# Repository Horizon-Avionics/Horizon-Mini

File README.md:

# H²

## Building an open source flight logger

### By Scooter Y and Liam G

------

#### About:

The Goal of this project was to build a simpler datalogger for model rockets to collect the info needed for most rocketiers from multiple sensors including an IMU and Baro. We built this as a dev board so when we eventually produce the larger V1 board, we can weed out issues before spending $400.

#### Features:

- This whole board is under $50 USD.
- One ARMCortex M0+ MCU
- IMU and Barometer
- SD and NAND Datalogging

##### Checkout locally

1. `git clone https://github.com/Horizon-Avionics/Horizon-Mini`

2. Open the corresponding folder in KiCad 9.0

### Some Photos So Far

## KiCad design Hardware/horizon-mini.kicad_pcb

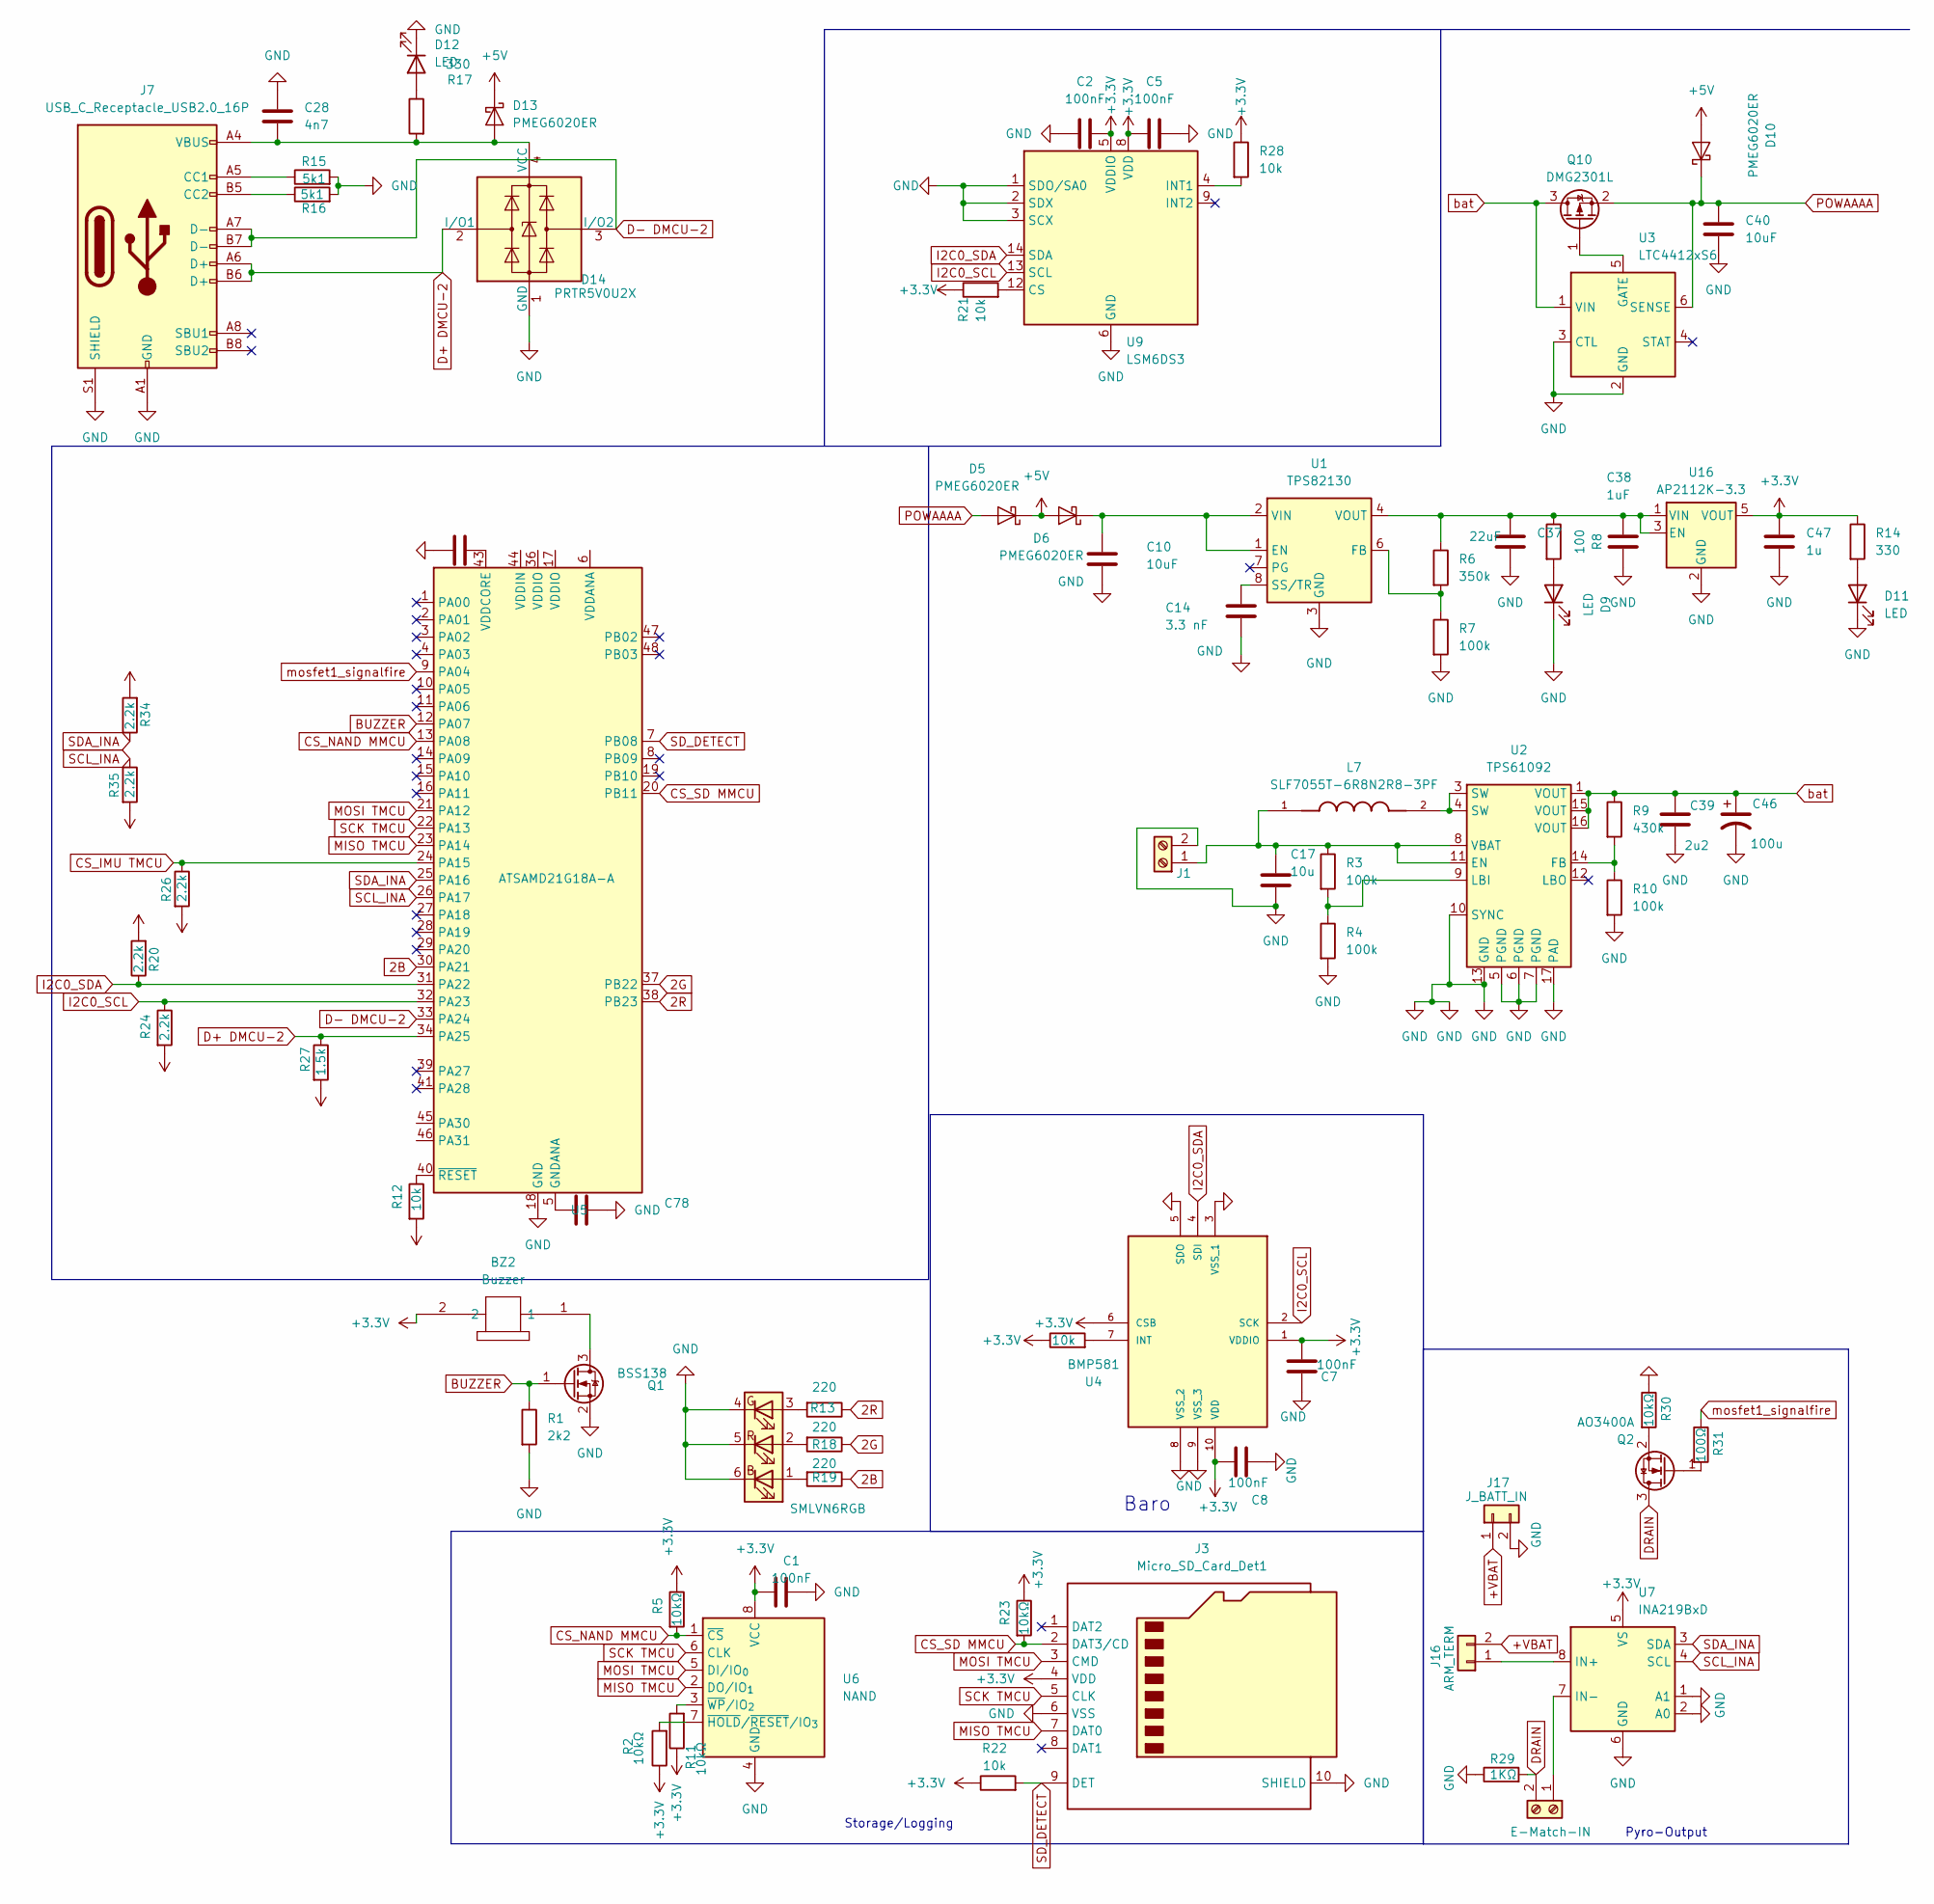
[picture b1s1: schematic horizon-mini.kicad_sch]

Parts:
BZ2: Buzzer; MLT-8530_JHE
C1, C2, C5, C7, C8, C78: 100nF; C_0402_1005Metric
C6: F1uF; C_0402_1005Metric
C10, C40: 10uF; C_0402_1005Metric
C14: 3.3 nF; C_0402_1005Metric
C17: 10u; C_0402_1005Metric
C28: 4n7; C_0402_1005Metric
C37: 22uF; C_0402_1005Metric
C38: 1uF; C_0402_1005Metric
C39: 2u2; C_0402_1005Metric
C46: 100u; C_0402_1005Metric
C47: 1u; C_0402_1005Metric
D1: SMLVN6RGB; LED_ROHM_SMLVN6
D5, D6, D10, D13: PMEG6020ER; Nexperia_CFP3_SOD-123W
D9, D11, D12: LED; LED_0603_1608Metric
D14: PRTR5V0U2X; SOT-143
J1: Screw_Terminal_01x02; TerminalBlock_Phoenix_MPT-0,5-2-2.54_1x02_P2.54mm_Horizontal
J3: Micro_SD_Card_Det1; microSD_HC_Hirose_DM3D-SF
J4: E-Match-IN; TerminalBlock_Phoenix_MPT-0,5-2-2.54_1x02_P2.54mm_Horizontal
J7: USB_C_Receptacle_USB2.0_16P; USB_C_Receptacle_GCT_USB4105-xx-A_16P_TopMnt_Horizontal
J16: ARM_TERM; PinHeader_1x02_P1.27mm_Vertical
J17: J_BATT_IN; PinHeader_1x02_P1.27mm_Vertical
L7: SLF7055T-6R8N2R8-3PF; L_7.3x7.3_H4.5; PARTREV N/A
Q1: BSS138; SOT-23
Q2: AO3400A; SOT-23
Q10: DMG2301L; SOT-23
R1: 2k2; R_0402_1005Metric
R2, R5, R11, R23, R30: 10kΩ; R_0402_1005Metric
R3, R4, R7, R10: 100k; R_0402_1005Metric
R6: 350k; R_0402_1005Metric
R8: 100; R_0402_1005Metric
R9: 430k; R_0402_1005Metric
R12, R21, R22, R28, R33: 10k; R_0402_1005Metric
R13, R18, R19: 220; R_0402_1005Metric
R14, R17: 330; R_0402_1005Metric
R15, R16: 5k1; R_0402_1005Metric
R20, R24, R26, R34, R35: 2.2k; R_0402_1005Metric
R27: 1.5k; R_0402_1005Metric
R29: 1KΩ; R_0402_1005Metric
R31: 100Ω; R_0402_1005Metric
U1: TPS82130; Texas_SIL0008D_MicroSiP-8-1EP_2.8x3mm_P0.65mm_EP1.1x1.9mm_T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
U2: TPS61092; Texas_RSA_VQFN-16-1EP_4x4mm_P0.65mm_EP2.7x2.7mm_ThermalVias
U3: LTC4412xS6; TSOT-23-6
U4: BMP581; Manufacturer_Part_Number BMP581
U5: ATSAMD21G18A-A; TQFP-48_7x7mm_P0.5mm
U6: NAND; SOIC-8_5.3x5.3mm_P1.27mm
U7: INA219BxD; SOIC-8_3.9x4.9mm_P1.27mm
U9: LSM6DS3; LGA-14_3x2.5mm_P0.5mm_LayoutBorder3x4y
U16: AP2112K-3.3; SOT-23-5

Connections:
2B: R19.1, U5.30 (PA21)
2G: R18.1, U5.37 (PB22)
2R: R13.1, U5.38 (PB23)
+3.3V: BZ2.2, C1.1, C2.2, C5.2, C7.2, C8.2, C47.1, J3.4 (VDD), R2.1, R5.1, R11.1, R12.2, R14.1, R20.2, R21.1, R22.1, R23.1, R24.2, R26.2, R27.2, R28.1, R33.1, R34.2, R35.2, U4.1 (VDDIO), U4.6 (CSB), U4.10 (VDD), U6.8 (VCC), U7.5 (VS), U9.5 (VDDIO), U9.8 (VDD), U16.5 (VOUT)
+5V: D5.1 (K), D6.2 (A), D10.2 (A), D13.1 (K)
+VBAT: J16.2, J17.1
BUZZER: Q1.1 (G), R1.1, U5.12 (PA07)
CS_IMU TMCU: R26.1, U5.24 (PA15)
CS_NAND MMCU: R5.2, U5.13 (PA08), U6.1 (~CS)
CS_SD MMCU: J3.2 (DAT3/CD), R23.2, U5.20 (PB11)
D+ DMCU-2: D14.2 (I/O1), J7.A6 (D+), J7.B6 (D+), R27.1, U5.34 (PA25)
D- DMCU-2: D14.3 (I/O2), J7.A7 (D-), J7.B7 (D-), U5.33 (PA24)
DRAIN: J4.2, Q2.3 (D), R29.2
GND: C1.2, C2.1, C5.1, C6.2, C7.1, C8.1, C10.2, C14.2, C17.2, C28.1, C37.2, C38.2, C39.2, C40.2, C46.2, C47.2, C78.1, D1.4 (GK), D1.5 (RK), D1.6 (BK), D9.1 (K), D11.1 (K), D12.1 (K), D14.1 (GND), J1.2, J3.6 (VSS), J3.10 (SHIELD), J7.A1 (GND), J7.A12 (GND), J7.B1 (GND), J7.B12 (GND), J7.S1 (SHIELD), J17.2, Q1.2 (S), R1.2, R4.2, R7.2, R10.2, R15.2, R16.2, R29.1, R30.1, U1.3 (GND), U1.9 (GND), U2.5 (PGND), U2.6 (PGND), U2.7 (PGND), U2.10 (SYNC), U2.13 (GND), U2.17 (PAD), U3.2 (GND), U3.3 (CTL), U4.3 (VSS_1), U4.5 (SDO), U4.8 (VSS_2), U4.9 (VSS_3), U5.18 (GND), U5.35 (GND), U5.42 (GND), U6.4 (GND), U7.1 (A1), U7.2 (A0), U7.6 (GND), U9.1 (SDO/SA0), U9.2 (SDX), U9.3 (SCX), U9.6 (GND), U9.7 (GND), U16.2 (GND); also elsewhere on the board
I2C0_SCL: R24.1, U4.2 (SCK), U5.32 (PA23), U9.13 (SCL)
I2C0_SDA: R20.1, U4.4 (SDI), U5.31 (PA22), U9.14 (SDA)
MISO TMCU: J3.7 (DAT0), U5.23 (PA14), U6.2 (DO/IO_{1})
MOSI TMCU: J3.3 (CMD), U5.21 (PA12), U6.5 (DI/IO_{0})
unnamed: D1.1 (BA), R19.2
unnamed: D1.3 (GA), R13.2
unnamed: D1.2 (RA), R18.2
unnamed: C10.1, D6.1 (K), U1.1 (EN), U1.2 (VIN)
unnamed: D9.2 (A), R8.2
unnamed: D11.2 (A), R14.2
unnamed: D12.2 (A), R17.1
unnamed 25: C28.2, D13.2 (A), D14.4 (VCC), J7.A4 (VBUS), J7.A9 (VBUS), J7.B4 (VBUS), J7.B9 (VBUS), R17.2; also elsewhere on the board
unnamed: C17.1, J1.1, L7.1, R3.1, U2.8 (VBAT), U2.11 (EN)
unnamed: J4.1, U7.7 (IN-)
unnamed: J7.A5 (CC1), R15.1
unnamed: J7.B5 (CC2), R16.1
unnamed: J16.1, U7.8 (IN+)
unnamed: L7.2, U2.3 (SW), U2.4 (SW)
unnamed: BZ2.1, Q1.3 (D)
unnamed: Q2.1 (G), R31.2
unnamed: Q2.2 (S), R30.2
unnamed: Q10.1 (G), U3.5 (GATE)
unnamed: R6.2, R7.1, U1.6 (FB)
unnamed: C14.1, U1.8 (SS/TR)
unnamed: R9.2, R10.1, U2.14 (FB)
unnamed: R3.2, R4.1, U2.9 (LBI)
unnamed: R33.2, U4.7 (INT)
unnamed: C78.2, U5.5 (GNDANA)
unnamed: C6.1, U5.43 (VDDCORE)
unnamed: R12.1, U5.40 (~RESET)
unnamed: R2.2, U6.7 (~HOLD/~RESET/IO_{3})
unnamed: R11.2, U6.3 (~WP/IO_{2})
unnamed: R21.2, U9.12 (CS)
unnamed: R28.2, U9.4 (INT1)
unnamed: C37.1, C38.1, R6.1, R8.1, U1.4 (VOUT), U1.5 (VOUT), U16.1 (VIN), U16.3 (EN)
POWAAAA: C40.1, D5.2 (A), D10.1 (K), Q10.2 (S), U3.6 (SENSE)
SCK TMCU: J3.5 (CLK), U5.22 (PA13), U6.6 (CLK)
SCL_INA: R35.1, U5.26 (PA17)
SDA_INA: R34.1, U5.25 (PA16)
SD_DETECT: J3.9 (DET), R22.2, U5.7 (PB08)
bat: C39.1, C46.1, Q10.3 (D), R9.1, U2.1 (VOUT), U2.15 (VOUT), U2.16 (VOUT), U3.1 (VIN)
mosfet1_signalfire: R31.1, U5.9 (PA04)

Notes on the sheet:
Pyro-Output
Storage/Logging
Baro

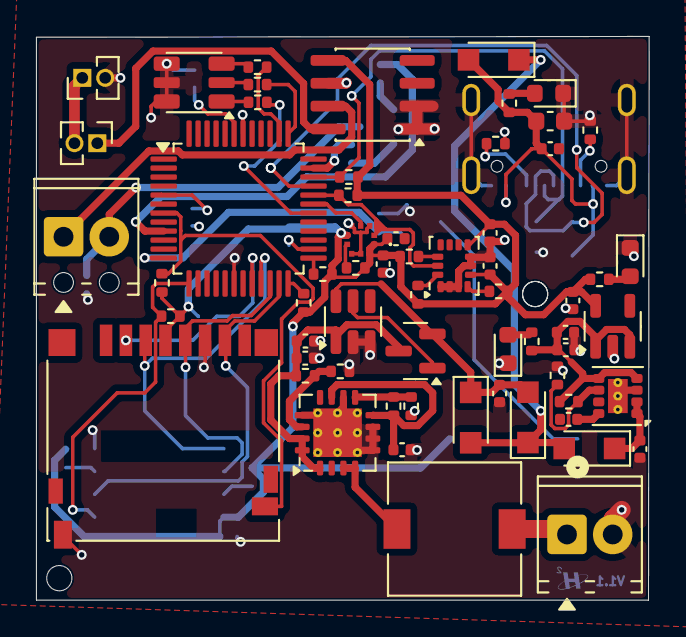
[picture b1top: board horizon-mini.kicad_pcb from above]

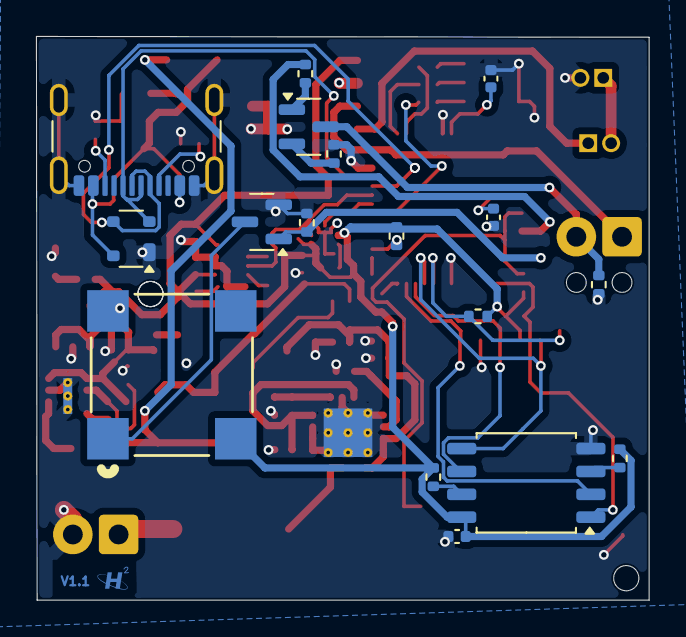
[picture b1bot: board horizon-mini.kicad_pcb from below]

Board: 2 copper layers, 34.0 x 31.3 mm, 79 parts (17 on the bottom side), 55 nets.

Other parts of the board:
C29: 100n; C_0603_1608Metric

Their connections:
GND: C29.1; also elsewhere on the board
unnamed 25: C29.2; also elsewhere on the board

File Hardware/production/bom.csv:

Designator,Footprint,Quantity,Value,LCSC Part #
"_4, _3, _2, ",,4,,
BZ2,MLT-8530_JHE,1,Buzzer,
"C1, C2, C3, C4, C5",0603,5,100nF,
"C10, C40",0603,2,10uF,
"C11, C7, C8, C9",0402,4,0.1uF,
C12,0402,1,10uF,
C14,0603,1,3.3 nF,
C17,0603,1,10u,
C28,0603,1,4n7,
C29,0603,1,100n,
C37,0603,1,22uF,
C38,0603,1,1uF,
C39,0603,1,2u2,
C46,1206,1,100u,
C47,0603,1,1u,
C6,0603,1,F1uF,
C78,0402,1,100nF,
D1,LED_ROHM_SMLVN6,1,SMLVN6RGB,
"D10, D13, D5, D6",Nexperia_CFP3_SOD-123W,4,PMEG6020ER,
"D11, D12, D2, D9",0603,4,LED,
D14,SOT-143,1,PRTR5V0U2X,
F2,0603,1,Polyfuse,
J1,"TerminalBlock_Phoenix_MPT-0,5-2-2.54_1x02_P2.54mm_Horizontal",1,Screw_Terminal_01x02,
J16,PinHeader_1x02_P2.00mm_Vertical_SMD_Pin1Left,1,arming terminal,
J2,TerminalBlock_MetzConnect_Type059_RT06302HBWC_1x02_P3.50mm_Horizontal,1,Conn_01x02_Pin,
J3,microSD_HC_Hirose_DM3D-SF,1,Micro_SD_Card_Det1,
J7,USB_C_Receptacle_GCT_USB4105-xx-A_16P_TopMnt_Horizontal,1,USB_C_Receptacle_USB2.0_16P,
J8,PinHeader_2x03_P2.54mm_Vertical,1,Conn_02x03_Counter_Clockwise,
L7,L_7.3x7.3_H4.5,1,SLF7055T-6R8N2R8-3PF,
Q1,SOT-23,1,BSS138,
Q10,SOT-23,1,DMG2301L,
Q2,SOT-23,1,IRLML6402,
R1,0603,1,2k2,
"R10, R3, R4, R7",0603,4,100k,
"R11, R2, R23",0603,3,10kΩ,
"R12, R21, R22, R25, R28, R29, R80",0603,7,10k,
"R13, R18, R19",0603,3,220,
"R14, R17",0603,2,330,
"R15, R16",0603,2,5k1,
"R20, R24, R26",0603,3,2.2k,
R27,0603,1,1.5k,
"R30, R8",0603,2,100,
R31,0603,1,1k,
R5,0402,1,10kΩ,
R6,0805,1,350k,
R9,0603,1,430k,
U1,Texas_SIL0008D_MicroSiP-8-1EP_2.8x3mm_P0.65mm_EP1.1x1.9mm_ThermalVias,1,TPS82130,
U16,SOT-23-5,1,AP2112K-3.3,
U2,Texas_RSA_VQFN-16-1EP_4x4mm_P0.65mm_EP2.7x2.7mm_ThermalVias,1,TPS61092,
U3,TSOT-23-6,1,LTC4412xS6,
U5,TQFP-48_7x7mm_P0.5mm,1,ATSAMD21G18A-A,
U6,SOIC-8_5.3x5.3mm_P1.27mm,1,NAND,
U7,ST_HLGA-10_2x2mm_P0.5mm_LayoutBorder3x2y,1,LPS22HB,
U9,LGA-14_3x2.5mm_P0.5mm_LayoutBorder3x4y,1,LSM6DS3,

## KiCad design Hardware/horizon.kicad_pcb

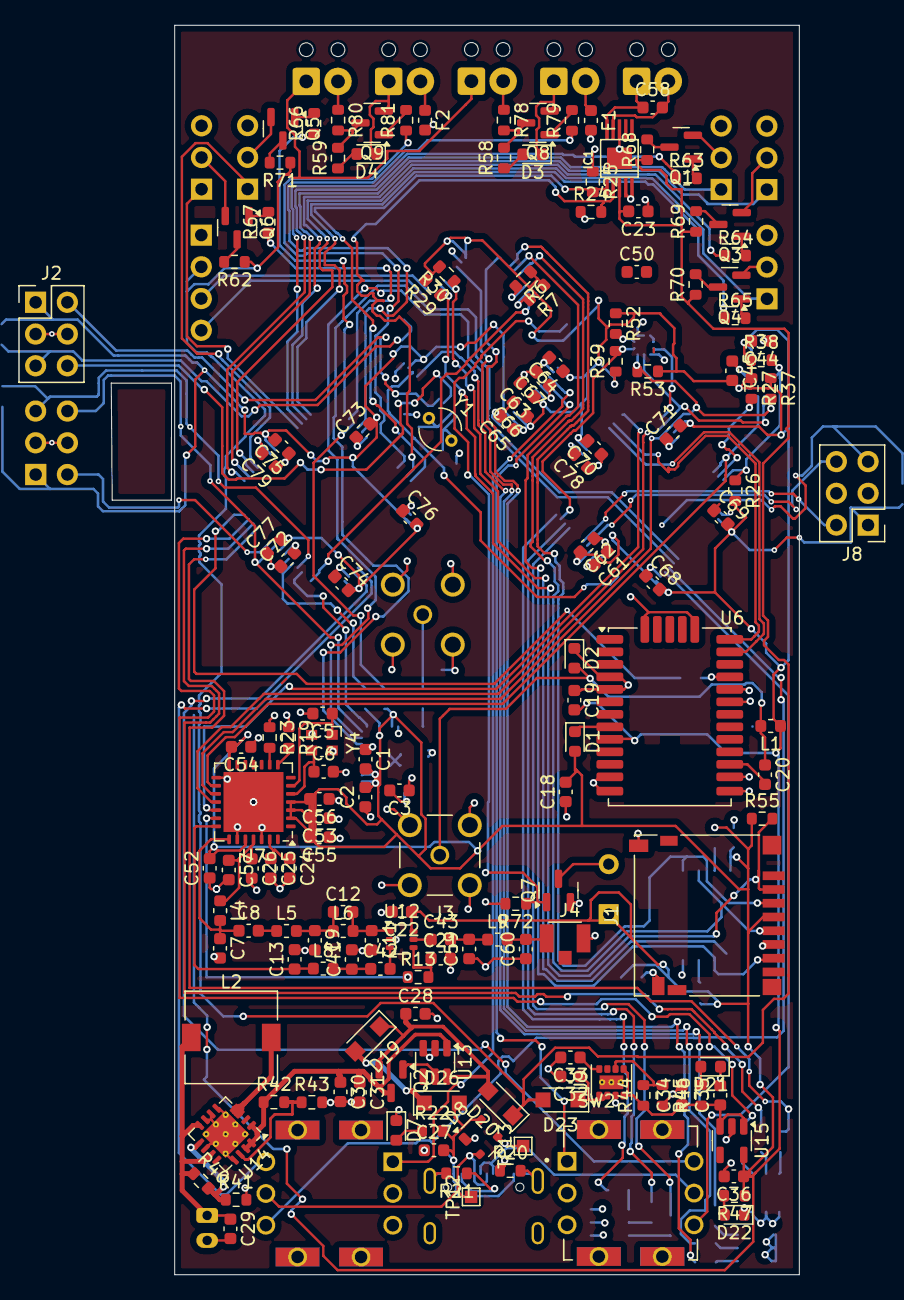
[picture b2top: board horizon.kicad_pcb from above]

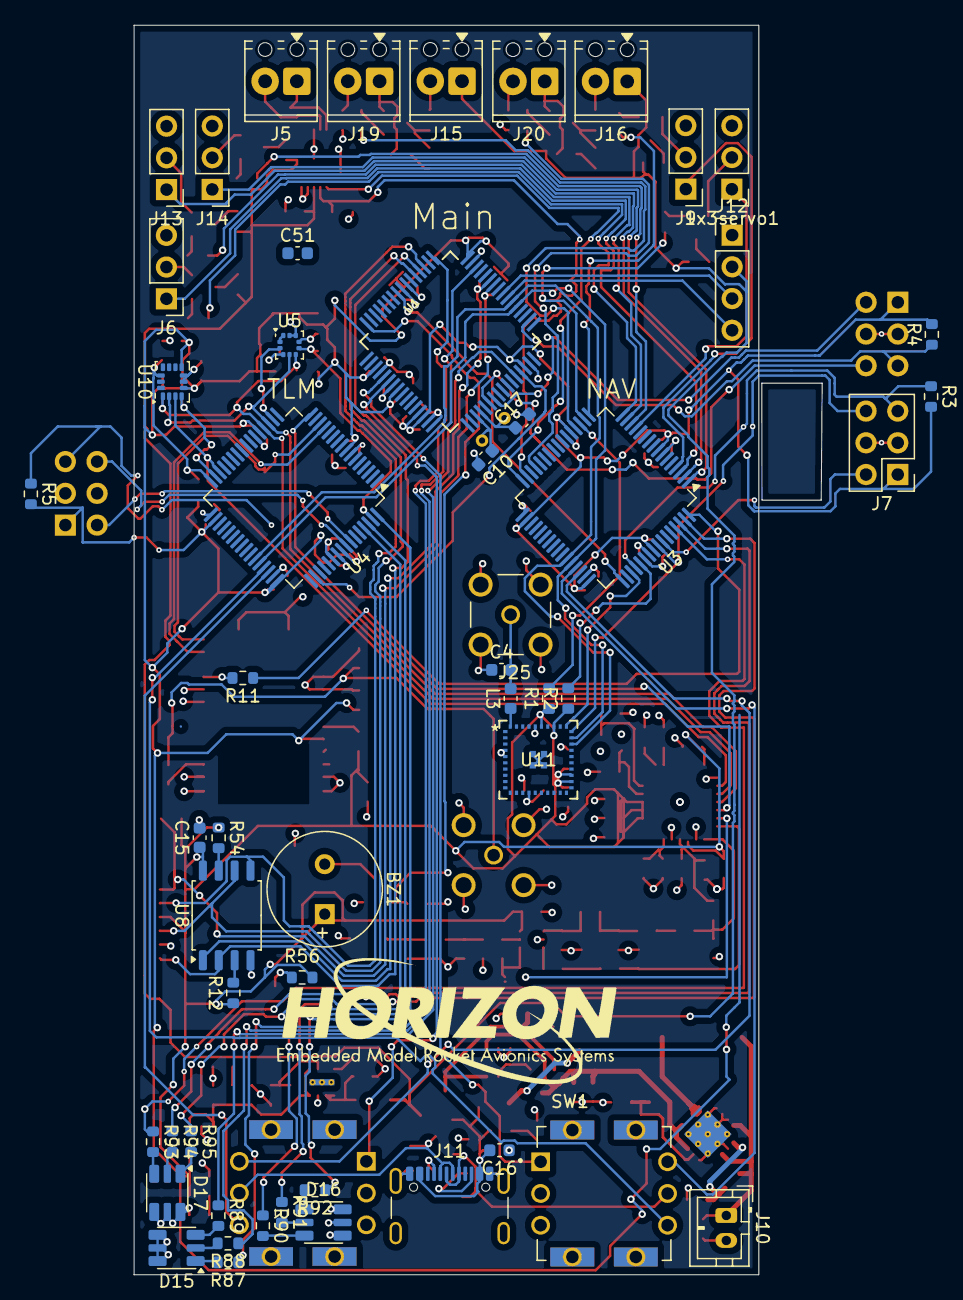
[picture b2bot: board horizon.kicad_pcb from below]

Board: 4 copper layers, 50.0 x 100.0 mm, 210 parts (53 on the bottom side), 164 nets.

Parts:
1x3servo1: Conn_01x03; PinHeader_1x03_P2.54mm_Vertical
BZ1: Buzzer; MagneticBuzzer_PUI_AT-0927-TT-6-R
C1, C2, C3, C23: 100 nF; C_0603_1608Metric
C4, C12: 1.2 pF; C_0603_1608Metric
C5, C6: 12 pF; C_0603_1608Metric
C7, C9, C13, C59: 2.2 pF; C_0603_1608Metric
C8: 1.5 pF; C_0603_1608Metric
C10, C17: 12pF; C_0603_1608Metric
C11, C41: 2.7 pF; C_0603_1608Metric
C15, C19, C20, C25, C44, C45, C50, C51, C52, C53, C54, C55, C56, C57, C58, C61, C62, C68, C69, C70, C71, C73, C74, C75, C76, C77, C78, C79: 100nF; C_0603_1608Metric
C16: 4n7; C_0603_1608Metric
C18, C67: 4.7uF; C_0603_1608Metric
C21, C22: 1nF; C_0603_1608Metric
C24, C26: 10nF; C_0603_1608Metric
C27: 100n; C_0603_1608Metric
C28, C32: 10uF; C_0603_1608Metric
C29: 10u; C_0603_1608Metric
C30: 2u2; C_0603_1608Metric
C31: 100u; C_0603_1608Metric
C33: 3.3 nF; C_0603_1608Metric
C34: 22uF; C_0603_1608Metric
C35, C63, C72: 1uF; C_0603_1608Metric
C36: 1u; C_0603_1608Metric
C42, C60: 1.8 pF; C_0603_1608Metric
C43: 1.0 pF; C_0603_1608Metric
C64, C65, C66: 0.1uF; C_0603_1608Metric
D1: D_Schottky; D_0603_1608Metric
D2: PESD5V‑S5ULC; D_0603_1608Metric
D3, D4, D7, D21, D22: LED; LED_0603_1608Metric
D8: PRTR5V0U2X; SOT-143
D15, D16, D17: SMLVN6RGB; LED_ROHM_SMLVN6
D19, D20, D23, D26: PMEG6020ER; Nexperia_CFP3_SOD-123W
F1, F2: Polyfuse; Fuse_0603_1608Metric
G**: LOGO
IC1: A3909; MSOP10-PAD
J1: Micro_SD_Card_Det1; microSD_HC_Hirose_DM3D-SF
J2, J7, J8: Conn_02x03_Counter_Clockwise; PinHeader_2x03_P2.54mm_Vertical
J3, J25: Conn_Coaxial; LPRS_SMA_CONNECTOR
J4: H9161TR-ND; HRS_U.FL-R-SMT_01_
J5: Screw_Term; TerminalBlock_Phoenix_MPT-0,5-2-2.54_1x02_P2.54mm_Horizontal
J6, J9, J13, J14: 1x3 servo; PinHeader_1x03_P2.54mm_Vertical
J10: Conn_01x02_Pin; JST_PH_B2B-PH-K_1x02_P2.00mm_Vertical
J11: USB_C_Receptacle_USB2.0_16P; USB_C_Receptacle_GCT_USB4105-xx-A_16P_TopMnt_Horizontal
J12: Conn_01x04; PinHeader_1x04_P2.54mm_Vertical
J15, J16: arming terminal; TerminalBlock_Phoenix_MPT-0,5-2-2.54_1x02_P2.54mm_Horizontal
J19, J20: Screw_Terminal_01x02; TerminalBlock_Phoenix_MPT-0,5-2-2.54_1x02_P2.54mm_Horizontal
L1: 47 nH; L_0603_1608Metric
L2: SLF7055T-6R8N2R8-3PF; L_7.3x7.3_H4.5
L3: 3.9 nH; L_0603_1608Metric
L4: 8.2 nH; L_0603_1608Metric
L5, L8: 6.8 nH; L_0603_1608Metric
L6, L9: 10 nH; L_0603_1608Metric
Q1, Q3, Q4, Q5, Q6, Q8, Q9: IRLML6402; SOT-23
Q2: DMG2301L; SOT-23
Q7: BSS138; SOT-23
R1, R2: 10 kΩ; R_0603_1608Metric
R3, R4, R5, R19, R23, R24, R25, R27, R37, R38, R39, R52, R53, R56, R78, R80: 10k; R_0603_1608Metric
R6, R7: 4.7k; R_0603_1608Metric
R11, R12, R54, R55: 10kΩ; R_0603_1608Metric
R13, R58, R59: 1k; R_0603_1608Metric
R20, R21: 5k1; R_0603_1608Metric
R22, R47: 330; R_0603_1608Metric
R26, R29, R30: R; R_0603_1608Metric
R40, R41, R43, R45, R62, R68, R69, R70, R71: 100k; R_0603_1608Metric
R42: 430k; R_0603_1608Metric
R44: 350k; R_0603_1608Metric
R46, R63, R64, R65, R66, R67, R79, R81: 100; R_0603_1608Metric
R72: 2k2; R_0603_1608Metric
R87, R88, R89, R90, R91, R92, R93, R94, R95: 220; R_0603_1608Metric
SW1, SW2: SW_SP3T; SW_NR01103ANG13-1C
TP12, TP13: TestPoint; TestPoint_Pad_1.0x1.0mm
U1: MMCU; QFP50P1200X1200X160-64N
U3: NMCU; TQFP-64_10x10mm_P0.5mm
U4: TMCU; TQFP-64_10x10mm_P0.5mm
U5: LPS22HB; ST_HLGA-10_2x2mm_P0.5mm_LayoutBorder3x2y
U6: GPS; Quectel_L96
U7: SX1276; QFN-28-1EP_6x6mm_P0.65mm_EP4.8x4.8mm
U8: NAND; SOIC-8_5.3x5.3mm_P1.27mm
U9: TPS82130; Texas_SIL0008D_MicroSiP-8-1EP_2.8x3mm_P0.65mm_EP1.1x1.9mm_T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
U10: LSM6DS3; LGA-14_3x2.5mm_P0.5mm_LayoutBorder3x4y
U11: BGM220SC12WGA2R
U12: PE4259; SOT-363_SC-70-6
U13: LTC4412xS6; TSOT-23-6
U14: TPS61092; Texas_RSA_VQFN-16-1EP_4x4mm_P0.65mm_EP2.7x2.7mm_ThermalVias
U15: AP2112K-3.3; SOT-23-5
Y1: Crystal; Crystal_AT310_D3.0mm_L10.0mm_Vertical
Y4: 32MHz; Crystal_SMD_Abracon_ABM10-4Pin_2.5x2.0mm

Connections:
1B: R87.1, U1.49 (D10/TX2/PWM)
1G: R88.1, U1.46 (D9/RX2/PWM)
1R: R89.1, U1.28 (D3/CAN-TX/PWM)
2B: R92.1, U4.64 (PB03)
2G: R91.1, U4.62 (PB01)
2R: R90.1, U4.61 (PB00)
3B: R95.1, U3.63 (PB02)
3G: R94.1, U3.62 (PB01)
3R: R93.1, U3.61 (PB00)
+3.3V: BZ1.1 (+), C1.2, C2.2, C15.1, C18.2, C19.2, C22.1, C36.1, C44.2, C45.2, C50.2, C51.2, C52.2, C53.2, C54.2, C55.2, C56.2, C62.2, C63.1, C64.1, C65.1, C66.1, C68.2, C69.2, C70.2, C71.2, C73.2, C74.2, C75.2, C76.2, C77.2, D1.2 (A), J1.4 (VDD), J2.1, J7.1, J8.1, L1.1, R1.1, R2.1, R3.2, R4.2, R5.2, R6.1, R7.1, R12.1, R26.2, R27.1, R29.2, R30.2, R37.1, R38.1, R39.1, R47.1, R52.1, R53.1, R54.1, R55.1, R56.1, U1.3 (VCC), U1.8 (VREGIN), U1.13 (VCCA), U1.14 (VREF-H), U1.21 (VBAT), U1.30 (VCC), U1.48 (VCC), U3.8 (VDDANA), U3.21 (VDDIO), U3.34 (VDDIO), U3.48 (VDDIO), U3.56 (VDDIN), U4.8 (VDDANA), U4.21 (VDDIO), U4.34 (VDDIO), U4.48 (VDDIO), U4.56 (VDDIN), U5.1 (Vdd_IO), U5.10 (VDD), U6.9 (VCC), U7.2 (VR_ANA), U7.3 (VBAT_ANA), U7.4 (VR_DIG), U7.14 (VBAT_DIG), U7.24 (VBAT_RF), U8.8 (VCC), U10.5 (VDDIO), U10.8 (VDD), U11.22 (VREGVDD), U11.23 (IOVDD), U11.33 (PC05), U11.35 (RESETn), U12.6 (VDD), U15.5 (VOUT)
+5V: C23.2, D20.1 (K), D23.2 (A), IC1.3 (VBB), J12.2, J15.1, J16.1, R62.1, R68.1, R69.1, R70.1, R71.1
BGM_CS: U3.51 (PA27), U11.31 (PC03)
BGM_INT: R2.2, U3.53 (PA28)
BGM_RESET: R1.2, U3.19 (PA10)
BUZZER: Q7.1 (G), R72.1, U1.64 (D5/PWM)
CAM_RX: J12.3, U1.40 (D1/TX1/TOUCH)
CAM_TX: J12.4, U1.39 (D0/RX1/TOUCH)
CS_BARO TMCU: R39.2, U4.63 (PB02), U5.6 (~CS)
CS_IMU TMCU: R26.1, R38.2, U4.32 (PA15), U10.12 (CS)
CS_NAND MMCU: R30.1, U1.43 (D15/A1/TOUCH), U8.1 (~CS)
CS_SD MMCU: J1.2 (DAT3/CD), R29.1, R55.2, U1.42 (D25/PWM/TOUCH)
D+ DMCU-1: SW1.2, U3.45 (PA24)
D+ DMCU-2: SW1.4, U4.45 (PA24)
D+ MMCU: SW1.1, U1.5 (USB-P)
D- DMCU-1: SW2.2, U3.46 (PA25)
D- DMCU-2: SW2.4, U4.46 (PA25)
D- MMCU: SW2.1, U1.6 (USB-M)
DIR1: IC1.2 (IN2), R24.2, U3.31 (PA14)
GND: 1x3servo1.3, C1.1, C2.1, C3.1, C4.1, C5.2, C6.2, C7.2, C9.2, C10.2, C11.2, C13.2, C15.2, C16.1, C17.2, C18.1, C19.1, C21.2, C22.2, C23.1, C24.2, C25.2, C26.2, C27.1, C28.2, C29.2, C30.2, C31.2, C32.2, C33.2, C34.2, C35.2, C36.2, C41.2, C44.1, C45.1, C50.1, C51.1, C52.1, C53.1, C54.1, C55.1, C56.1, C57.2, C59.1, C60.1, C61.1, C62.1, C63.2, C64.2, C65.2, C66.2, C67.2, C68.1, C69.1, C70.1, C71.1, C72.1, C73.1, C74.1, C75.1, C76.1, C77.1, C78.1, C79.1, D2.1 (K), D7.1 (K), D8.1 (GND), D15.4 (GK), D15.5 (RK), D15.6 (BK), D16.4 (GK), D16.5 (RK), D16.6 (BK), D17.4 (GK), D17.5 (RK), D17.6 (BK), D21.1 (K), D22.1 (K), F1.2, F2.2, IC1.4 (IN3), IC1.5 (IN4), IC1.8 (GND), IC1.TP (GND), J1.6 (VSS), J1.10 (SHIELD), J2.3, J2.4, J3.G1, J3.G2, J3.G3, J3.G4, J4.2 (Ext), J6.3, J7.3, J7.4, J8.3, J8.4, J9.3, J10.2, J11.A1 (GND), J11.A12 (GND), J11.B1 (GND), J11.B12 (GND), J11.S1 (SHIELD), J12.1, J13.3, J14.3, J25.G1, J25.G2, J25.G3, J25.G4, Q7.2 (S), R19.1, R20.2, R21.2, R23.1, R24.1, R25.1, R41.2, R43.2, R45.2, R72.2, U1.4 (VSS), U1.15 (VREF-L), U1.16 (VSSA), U1.31 (VSS), U1.47 (VSS), U3.22 (GND), U3.33 (GND), U3.47 (GND), U3.54 (GND), U4.22 (GND), U4.33 (GND), U4.47 (GND), U4.54 (GND), U5.3 (GND), U5.8 (GND), U5.9 (GND), U6.4 (GND), U6.5 (GND), U6.10 (GND), U6.11 (GND), U6.12 (GND), U6.13 (GND), U6.14 (GND), U6.15 (GND), U6.18 (GND), U6.19 (GND), U6.21 (GND), U6.22 (GND), U6.27 (GND), U6.31 (GND), U7.15 (GND), U7.23 (GND), U7.26 (GND), U7.29 (GND), U8.4 (GND), U9.3 (GND), U9.9 (GND), U10.6 (GND), U10.7 (GND), U11.4 (GND), U11.5 (GND), U11.36 (GND), U11.41 (GND), U11.42 (GND), U11.43 (GND), U11.44 (GND), U12.2 (GND), U13.2 (GND), U13.3 (CTL), U14.5 (PGND), U14.6 (PGND), U14.7 (PGND), U14.10 (SYNC), U14.13 (GND), U14.17 (PAD), U15.2 (GND), Y4.2, Y4.4
I2C0_SCL: U1.37 (D19/A5/SCL0/TOUCH), U3.44 (PA23), U4.44 (PA23), U11.29 (PC01)
I2C0_SDA: U1.38 (D18/A4/SDA0/TOUCH), U3.43 (PA22), U4.43 (PA22), U11.28 (PC00)
INTERRUPT TMCU: R27.2, U4.31 (PA14), U10.4 (INT1)
MISO TMCU: R37.2, R53.2, U4.20 (PA11), U5.5 (SA0), U7.17 (MISO), U10.1 (SDO/SA0)
MOSI TMCU: U4.19 (PA10), U5.4 (SDA), U7.18 (MOSI), U10.2 (SDX)
NAND_MISO MMCU: J1.7 (DAT0), U1.52 (D12/MISO), U8.2 (DO/IO_{1})
NAND_MOSI MMCU: J1.3 (CMD), U1.51 (D11/MOSI), U8.5 (DI/IO_{0})
unnamed: 1x3servo1.2, Q6.2 (S)
unnamed: BZ1.2 (-), Q7.3 (D)
unnamed: C8.2, L5.1
unnamed: C9.1, C12.1, L5.2, L6.1
unnamed: C41.1, C42.1, L8.2
unnamed: C43.2, C59.2, L9.1
unnamed: D1.1 (K), U6.8 (V_BCKP)
unnamed: C20.1, D2.2 (A), J3.1 (In), L1.2
unnamed: D3.2 (A), R58.1
unnamed: D3.1 (K), J19.1, Q8.2 (S)
unnamed: D4.2 (A), R59.1
unnamed: D4.1 (K), J20.1, Q9.2 (S)
unnamed: D7.2 (A), R22.1
unnamed: D8.2 (I/O1), J11.A6 (D+), J11.B6 (D+), SW1.3, TP12.1
unnamed: D8.3 (I/O2), J11.A7 (D-), J11.B7 (D-), SW2.3, TP13.1
unnamed: D15.1 (BA), R87.2
unnamed: D15.3 (GA), R89.2
unnamed: D15.2 (RA), R88.2
unnamed: D16.1 (BA), R92.2
unnamed: D16.3 (GA), R90.2
unnamed: D16.2 (RA), R91.2
unnamed: D17.1 (BA), R95.2
unnamed: D17.3 (GA), R93.2
unnamed: D17.2 (RA), R94.2
unnamed: D21.2 (A), R46.2
unnamed: D22.2 (A), R47.2
unnamed: C32.1, D23.1 (K), U9.1 (EN), U9.2 (VIN)
unnamed: C16.2, C27.2, D8.4 (VCC), D26.2 (A), J11.A4 (VBUS), J11.A9 (VBUS), J11.B4 (VBUS), J11.B9 (VBUS), R22.2
unnamed: C58.1, IC1.10 (OUT1), J5.1
unnamed: C58.2, IC1.9 (OUT2), J5.2
unnamed: C60.2, J4.1 (In), L9.2
unnamed: J6.2, Q4.2 (S)
unnamed: J9.2, Q5.2 (S)
unnamed: C29.1, J10.1, L2.1, R40.1, U14.8 (VBAT), U14.11 (EN)
unnamed: J11.A5 (CC1), R20.1
unnamed: J11.B5 (CC2), R21.1
unnamed: J13.2, Q3.2 (S)
unnamed: J14.2, Q1.2 (S)
unnamed: J15.2, R78.1
unnamed: J16.2, R80.1
unnamed: F1.1, J19.2
unnamed: F2.1, J20.2
unnamed: C4.2, J25.1 (In), L3.2
unnamed: L2.2, U14.3 (SW), U14.4 (SW)
unnamed: Q1.3 (D), R68.2
unnamed: Q1.1 (G), R63.2
unnamed: Q2.1 (G), U13.5 (GATE)
unnamed: Q3.3 (D), R69.2
unnamed: Q3.1 (G), R64.2
unnamed: Q4.3 (D), R70.2
unnamed: Q4.1 (G), R65.2
unnamed: Q5.3 (D), R71.2
unnamed: Q5.1 (G), R66.2
unnamed: Q6.3 (D), R62.2
unnamed: Q6.1 (G), R67.2
unnamed: Q8.3 (D), R58.2, R78.2
unnamed: Q8.1 (G), R79.2
unnamed: Q9.3 (D), R59.2, R80.2
unnamed: Q9.1 (G), R81.2
unnamed: C17.1, U1.20 (EXTAL32), Y1.1
unnamed: C67.1, U1.7 (VOUT3V3)
unnamed: C10.1, U1.19 (XTAL32), Y1.2
unnamed: C79.2, U3.7 (GNDANA)
unnamed: C72.2, U3.55 (VDDCORE)
unnamed: C78.2, U4.7 (GNDANA)
unnamed: C61.2, U4.55 (VDDCORE)
unnamed: R52.2, U5.7 (INT_DRDY)
unnamed: C20.2, U6.16 (RF_OUT)
unnamed: R11.2, U6.23 (~RESET)
unnamed: R19.2, U7.8 (DIO0)
unnamed: R23.2, U7.9 (DIO1)
unnamed: C24.1, C25.1, U7.27 (PA_BOOST)
unnamed: R54.2, U8.7 (~HOLD/~RESET/IO_{3})
unnamed: R12.2, U8.3 (~WP/IO_{2})
unnamed: R44.2, R45.1, U9.6 (FB)
unnamed: C33.1, U9.8 (SS/TR)
unnamed: L3.1, U11.40 (ANT_OUT)
unnamed: C3.2, U11.14 (DECOUPLE)
unnamed: C21.1, R13.2, U12.4 (CTRL)
unnamed: C11.1, C12.2, L6.2, U12.1 (RF1)
unnamed: C42.2, U12.3 (RF2)
unnamed: C43.1, U12.5 (RFIN)
unnamed: R42.2, R43.1, U14.14 (FB)
unnamed: R40.2, R41.1, U14.9 (LBI)
unnamed: C34.1, C35.1, R44.1, R46.1, U9.4 (VOUT), U9.5 (VOUT), U15.1 (VIN), U15.3 (EN)
POWAAAA: C28.1, D19.1 (K), D20.2 (A), Q2.2 (S), U13.6 (SENSE)
PTA12: U1.29 (D4/CAN-RX/PWM), U4.50 (PB23)
PTD4: U1.57 (D2), U3.49 (PB22)
PWM1: IC1.1 (IN1), R25.2, U3.32 (PA15)
RFI_HF: C13.1, L8.1, U7.21 (RFI_HF)
RFO_HF: C7.1, C8.1, L4.2, U7.22 (RFO_HF)
RF_CS: U4.16 (PA07), U7.19 (NSS)
RS_GPS TMCU: R11.1, U3.64 (PB03)
RX TMCU: U4.14 (PA05), U6.26 (RXD1)
RXTX: R13.1, U7.20 (RXTX/RF_MOD)
SCK TMCU: U4.18 (PA09), U5.2 (SCL)
SD_DETECT: J1.9 (DET), R56.2
SERVO1: J14.1, U3.1 (PA00)
SERVO2: J13.1, U3.2 (PA01)
SERVO3: J6.1, U3.3 (PA02)
SERVO4: J9.1, U3.4 (PA03)
SERVO5: 1x3servo1.1, U3.13 (PA04)
SPI0_SCK MMCU: J1.5 (CLK), U1.53 (D28/A17), U8.6 (CLK)
SPI_CLOCK TMCU: U4.30 (PA13), U7.16 (SCK), U10.3 (SCX)
SWCLK DMCU-1: J7.6, U3.57 (PA30), U11.30 (PC02)
SWCLK DMCU-2: J8.6, U4.57 (PA30)
SWCLK MMCU: J2.6, U1.22 (PTA0)
SWDIO DMCU-1: J7.2, U3.58 (PA31)
SWDIO DMCU-2: J8.2, U4.58 (PA31)
SWDIO MMCU: J2.2, U1.23 (PTA1)
SX_XTA: C6.1, U7.5 (XTA), Y4.3
SX_XTB: C5.1, U7.6 (XTB), Y4.1
TX TMCU: U4.13 (PA04), U6.25 (TXD1)
VBUS: D19.2 (A), D26.1 (K)
VR_PA: C26.1, C57.1, L4.1, U7.25 (VR_PA)
bat: C30.1, C31.1, Q2.3 (D), R42.1, U13.1 (VIN), U14.1 (VOUT), U14.15 (VOUT), U14.16 (VOUT)
mosfet1_signal: R63.1, U3.14 (PA05)
mosfet1_signalfire: R79.1, U3.20 (PA11)
mosfet2_signal: R64.1, U3.15 (PA06)
mosfet2_signalfire: R81.1, U3.29 (PA12)
mosfet3_signal: R65.1, U3.16 (PA07)
mosfet4_signal: R66.1, U3.17 (PA08)
mosfet5_signal: R67.1, U3.18 (PA09)
nRESET DMCU-1: J7.5, R3.1, U3.52 (~RESET)
nRESET DMCU-2: J8.5, R5.1, U4.52 (~RESET)
nRESET MMCU: J2.5, R4.1, U1.34 (RESET)
scl: R6.2, U1.55 (D29/A18/SCL1)
sda: R7.2, U1.56 (D30/A19/SDA1)

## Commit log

2025-06-29 added kicad project
2025-06-29 added main board files
2025-06-29 added mainboard files
2025-06-29 Deleted unneeded chips and changes sensors from spi to i2c
2025-06-29 moved files to folders
2025-06-29 deleted unneeded files
2025-06-29 deleted MORE files
2025-06-30 starting first routing
2025-06-30 idk more changes
2025-06-30 traces v1
2025-06-30 routes v2!!!!
2025-07-08 finish v2 traces
2025-07-08 Re-started routing, like 3/4 done parts placement
2025-07-08 parts placement is done
2025-07-08 board routing is finally done... DRC errors look fake to me, but need to be double checked
2025-07-09 trying to revert
2025-07-09 uuuh, fixed shematic and re-did most of the routing for the new MCU :(
2025-07-09 Revert "Merge branch 'main' of https://github.com/Horizon-Avionics/Horizon-Mini"
    This reverts commit 9a022c3cd95984122db224f561db0d5bee869fb2, reversing
    changes made to 44f91161868ebb609577ad71ea77d3c9bc8dd4bf.
2025-07-09 revert
2025-07-09 Wiring take 2 is done- just a few DRC errors left
2025-07-09 deleted unneded files and added software folder
2025-07-09 fixed software and added platformio
2025-07-09 added headers
2025-07-09 added imu library and basic readings
2025-07-09 added speed and velocity formulas
2025-07-09 bmu code!
2025-07-09 Update JOURNAL up to day 4
2025-07-09 forgot to push...
2025-07-09 led is started(need mucho mas trabajo)
2025-07-10 readme update
2025-07-10 finished led logic shit
2025-07-10 Finally done... DRC look good, PCB is good, and schematic looks good!
2025-07-10 day 4/5 done neeed to add pic
2025-07-10 now final ;)... Needed to switch the 100uF to 0206, since 0603's for that just don't exist!
2025-07-10 final take 2 ;). Now no JLC DFM errors either!
2025-07-10 update reame and journal (STILL NEED TO UPDATE PHOTOS)
2025-07-11 the final final one
2025-07-11 Finish JOURNAL.md
2025-07-11 working compile (i think?)
2025-07-11 i̶t̶'s̶ a̶l̶l̶ d̶o̶w̶n̶ h̶i̶l̶l̶ f̶r̶o̶m̶ h̶e̶r̶e̶ f̶r̶i̶e̶n̶d̶s̶
2025-07-14 getting somewhere take 2
2025-07-14 DRC and some PCB routing stuff
2025-07-14 routing v2 should be done
2025-07-14 please liam fix decop caps
2025-07-14 software stuff idk
2025-07-14 fixed decop caps schematic and routes (plz check my work scooter)
2025-07-14 maybe good?
2025-07-14 ready for submission v2!
2025-07-14 Revert "Merge branch 'main' of https://github.com/Horizon-Avionics/Horizon-Mini"
    This reverts commit 679f00b043b1fbfec2143f9512c96a76483b1c63, reversing
    changes made to 3d15d739e12ed0ad8f757afd069957ffb8171449.
2025-07-14 forgot to push
2025-07-14 finished routes v2 and "fixed" drc
    ready for more bullying!
2025-07-14 submission time!
2025-07-15 the board has been stitched!
2025-07-15 fixed schematic
    i hate github
2025-07-16 add prod files
2025-07-16 what happened to the schemtaic lol?
2025-07-17 gotta keep the commit streak going ;)
2025-07-17 wooooah, found an error.. all good now!
2025-07-18 adding pyro schematic stuff
2025-07-18 push
2025-07-18 5.08mm terminal
2025-07-22 Revert "Merge branch 'main' of https://github.com/Horizon-Avionics/Horizon-Mini"
    This reverts commit 832f827b9a251a47b3d6c5f971ce72bc000230f5, reversing
    changes made to 952e8a21e36a298005532ab4306c205f1d35711e.
2025-07-22 what the github commits did I just figure out how to do
2025-07-22 uuuh, starting buzzer wiring while I'm waiting for max's amazing footprint ;)
2025-07-22 hold up, push time
2025-07-24 please look it over, I'm finished with it
2025-07-25 forgot to push from last night. Very small silscreen changes and stuff
2025-07-27 woops, git revert works too strong
2025-08-01 changed to zephyrRTOS
2025-08-01 started adding filter code
2025-08-01 changed filter code for sensor layout (liam needs to set the values in filter)
2025-08-01 fixed errors (oopsie woopsie :3)
2025-08-01 i did some things, just look at the files...
2025-08-20 continued work towards zephyr transfer
2025-08-20 more work, but very broken
2025-09-25 @mpkendall review before ordering pplllease. I fixed the data lines.
2025-10-27 added exponential moving average (EMA)
2025-10-27 @mpkendall please review before ordering.
2025-11-07 fixed the data lines. @mpkendall please review so we don't need x3 :)
    no gerber's were exported for this.
2025-11-09 regen gerber baby files
2025-11-09 @starry-liam please re-gen gerbers: fixed schematic parity
2025-11-09 bye bye old gerbers
2025-11-09 final gerbers???
2025-11-11 ema stuff and periodic folder
2025-11-11 keeping the commit count high
2025-11-11 applied EMA to periodic
2025-11-11 add packet creator
2025-11-11 started nand, added variant for RGB pins
2025-11-11 ill redo LED later it was cuasing trouble
2025-11-11 goofy shit but working build
2025-12-22 added resistors in series with D+/D- and flipped inductor to other side
2026-02-01 Changed the Baro to the higher accuracy one, and worked on re-doing the pyro-output... almost done it!
2026-02-26 ah yes, I love that I forgot to push lol. Fixed pyro + rerouted to save space.
2026-02-26 added prod files
